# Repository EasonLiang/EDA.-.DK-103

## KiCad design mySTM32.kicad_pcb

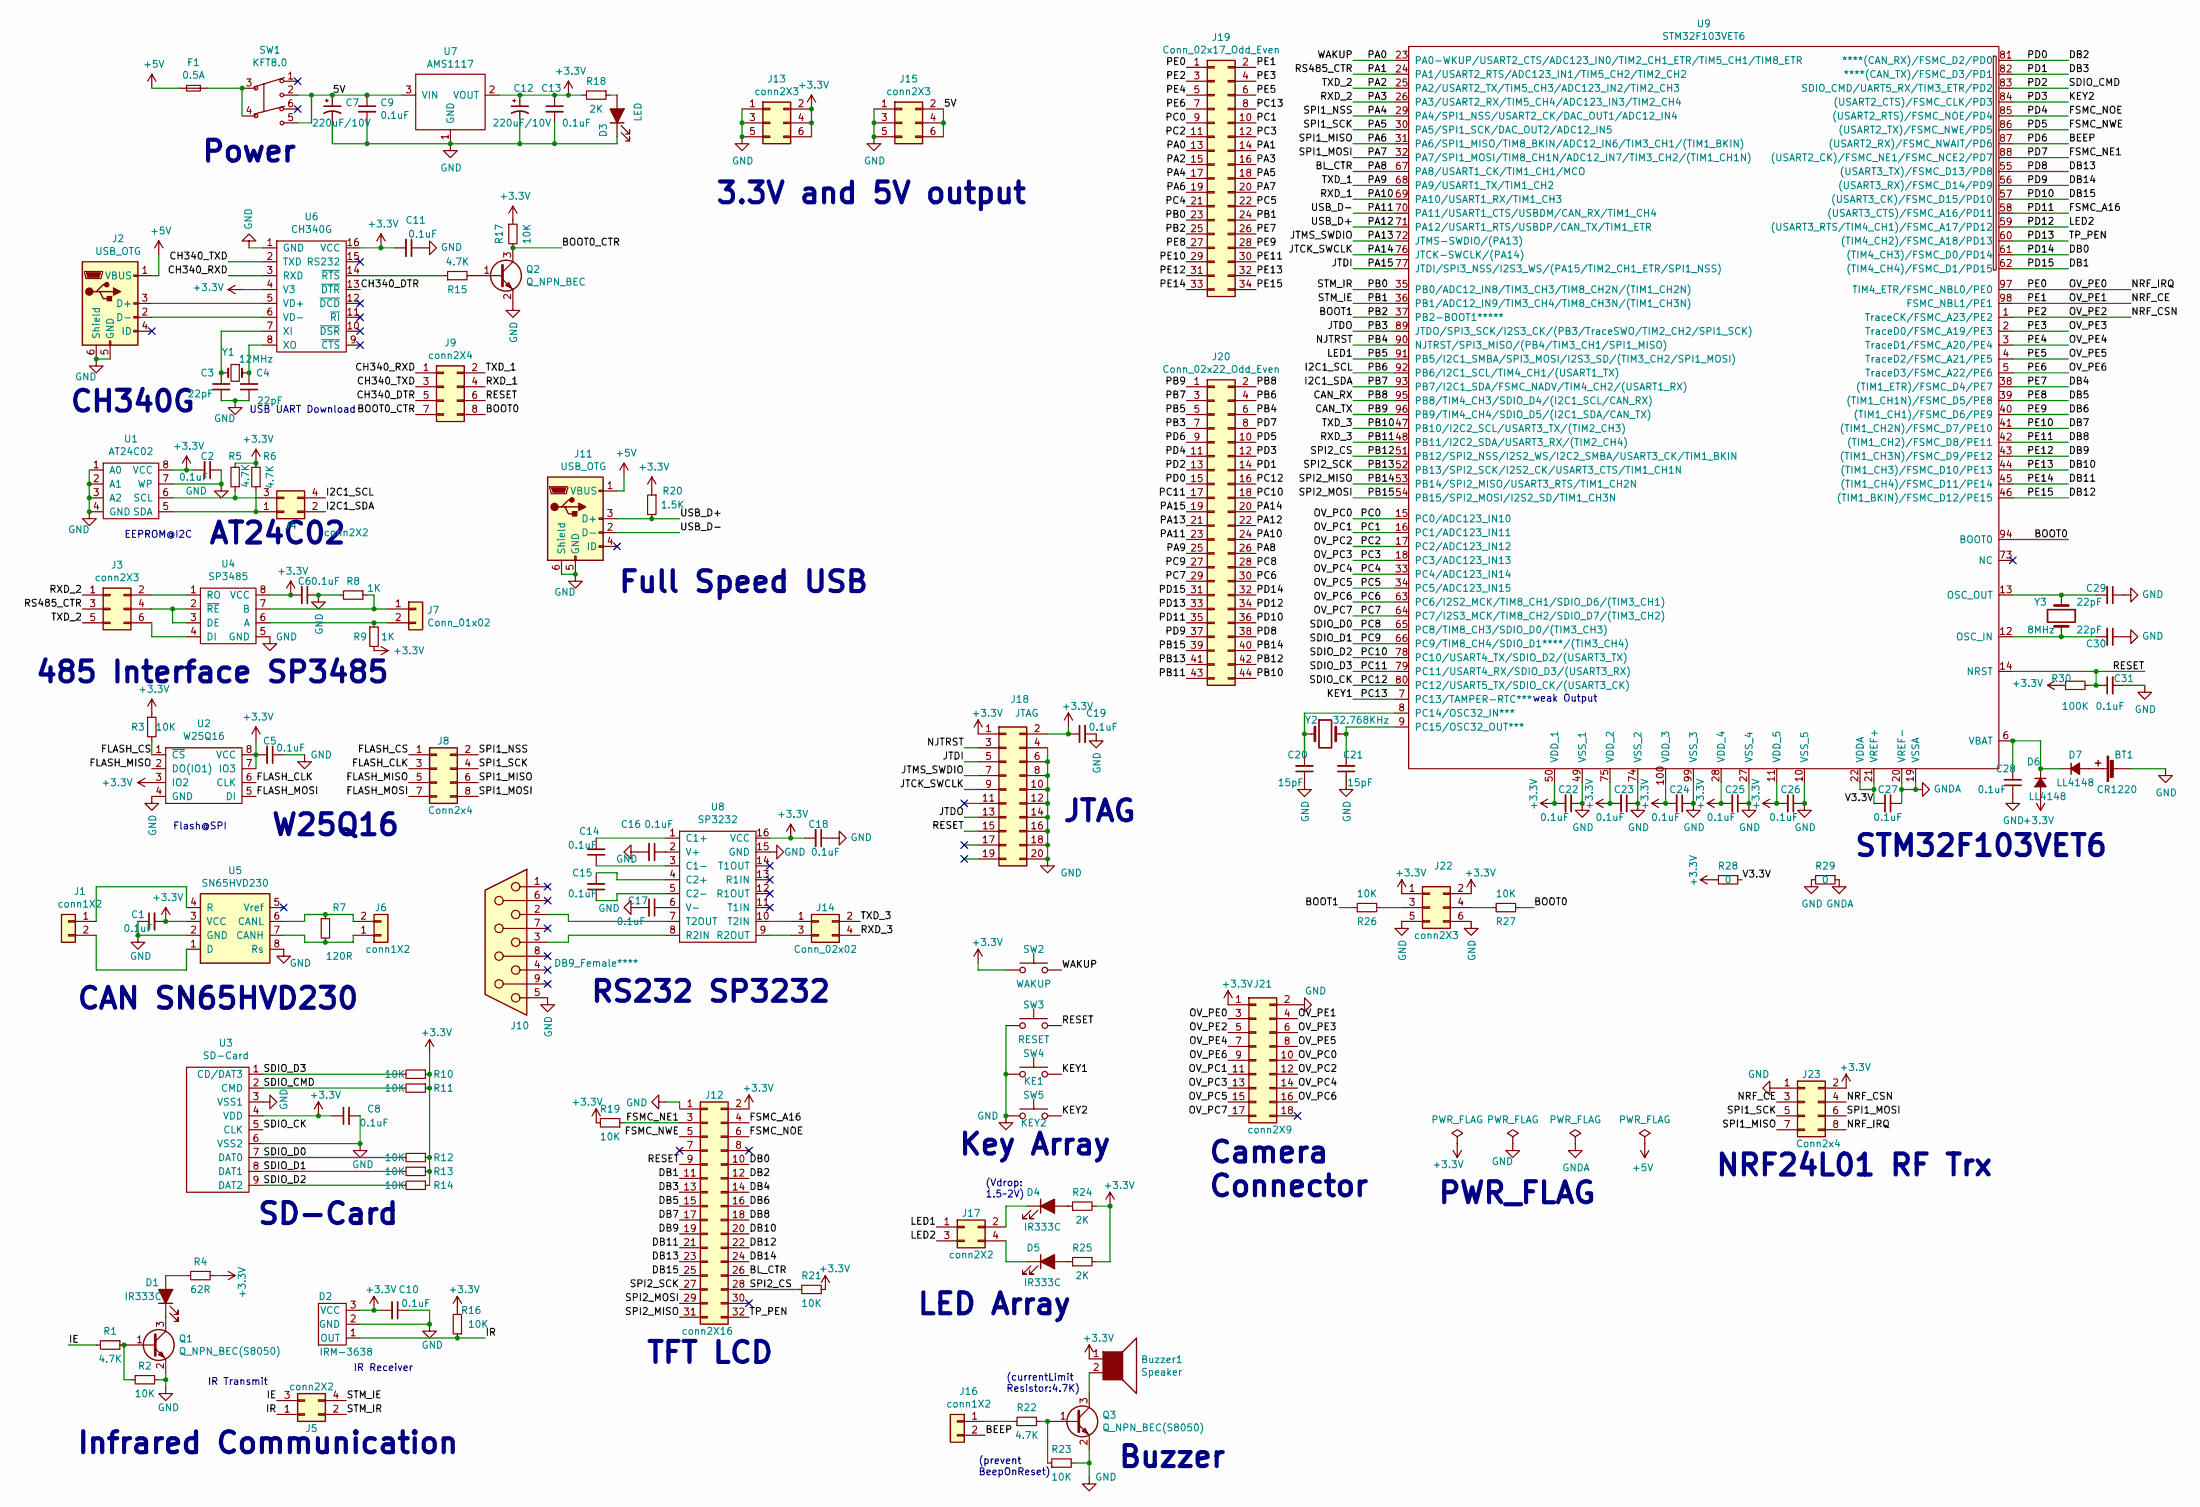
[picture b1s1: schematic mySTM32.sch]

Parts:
BT1: CR1220
Buzzer1: Speaker; BEEP9X5.5
C1, C2, C5, C6, C8, C10, C11, C14, C15, C16, C17, C18, C19, C22, C23, C24, C25, C26, C27, C28, C31: 0.1uF; C_0603_1608Metric
C3, C4, C29, C30: 22pF; C_0603_1608Metric
C7, C12: 220uF/10V; CP_Elec_6.3x5.7
C9, C13: 0.1uF; C_0805_2012Metric
C20, C21: 15pF; C_0603_1608Metric
D1: IR333C
D2: IRM-3638
D3: LED; LED_0805
D4, D5: IR333C; LED_0805
D6, D7: LL4148; LL34
F1: 0.5A; R_0805_2012Metric
J1, J16: conn1X2; CON1X2
J2, J11: USB_OTG; USB_Mini-B_Lumberg_2486_01_Horizontal
J3, J13, J15, J22: conn2X3; CON2X3
J4, J5, J17: conn2X2; CON2X2
J6: conn1X2; WJ301V-5.00-2P
J7: Conn_01x02; WJ301V-5.00-2P
J8, J23: Conn2x4; CON2X4
J9: conn2X4; CON2X4
J10: DB9_Female****; DB9FC
J12: conn2X16; CON2X16
J14: Conn_02x02; CON2X2
J18: JTAG; IDC-Header_2x10_P2.54mm_Vertical
J19: Conn_02x17_Odd_Even; CON2X17
J20: Conn_02x22_Odd_Even; CON2X22
J21: conn2X9; CON2X9
Q1, Q3: Q_NPN_BEC(S8050); SOT-23
Q2: Q_NPN_BEC; SOT-23
R1, R5, R6, R15, R22: 4.7K; R_0603_1608Metric
R2, R3, R10, R11, R12, R13, R14, R16, R17, R19, R21, R23, R26, R27: 10K; R_0603_1608Metric
R4: 62R; R_0805_2012Metric
R7: 120R; R_0603_1608Metric
R8, R9: 1K; R_0603_1608Metric
R18, R24, R25: 2K; R_0603_1608Metric
R20: 1.5K; R_0603_1608Metric
R28, R29: 0; R_0603_1608Metric
R30: 100K; R_0603_1608Metric
SW1: KFT8.0
SW2: WAKUP; KEY6X6
SW3: RESET; KEY6X6
SW4: KE1; KEY6X6
SW5: KEY2; KEY6X6
U1: AT24C02; SOIC-8
U2: W25Q16; WSOP-8
U3: SD-Card
U4: SP3485; SOIC-8
U5: SN65HVD230; SOIC-8
U6: CH340G; SOIC-16
U7: AMS1117; SOT-223
U8: SP3232; SOIC-16
U9: STM32F103VET6; LQFP-100
Y1: 12MHz; Crystal_HC49-U_Vertical
Y2: 32.768KHz; Crystal_SMD_3215-2Pin_3.2x1.5mm
Y3: 8MHz; Crystal_HC49-U_Vertical

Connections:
+3V3: Buzzer1.1, C1.2, C2.2, C5.2, C6.2, C8.1, C10.2, C11.2, C12.1, C13.1, C18.2, C19.1, C22.2, C23.2, C24.2, C25.2, C26.2, D2.3 (VCC), D6.2 (A), J12.2, J13.2, J13.4, J13.6, J18.1, J18.2, J21.1, J22.1, J22.2, J23.2, R3.1, R4.1, R5.2, R6.2, R9.2, R10.1, R11.1, R12.1, R13.1, R14.1, R16.2, R17.1, R18.2, R19.2, R20.1, R21.2, R24.2, R25.2, R28.2, R30.1, SW2.1, U1.8 (VCC), U2.3 (IO2), U2.7 (IO3), U2.8 (VCC), U3.4 (VDD), U4.8 (VCC), U5.3 (VCC), U6.4 (V3), U6.16 (VCC), U7.2 (VOUT), U8.16 (VCC), U9.11 (VDD_5), U9.28 (VDD_4), U9.50 (VDD_1), U9.75 (VDD_2), U9.100 (VDD_3)
+5V: F1.1, J2.1 (VBUS), J11.1 (VBUS)
/5V: C7.1, C9.1, J15.2, J15.4, J15.6, SW1.2, SW1.5, U7.3 (VIN)
/BEEP: J16.2, J20.9, U9.87 ((USART2_RX)/FSMC_NWAIT/PD6)
/BL_CTR: J12.26, J20.26, U9.67 (PA8/USART1_CK/TIM1_CH1/MCO)
/BOOT0: J9.8, R27.2, U9.94 (BOOT0)
/BOOT0_CTR: J9.7, Q2.3 (C), R17.2
/BOOT1: J19.25, R26.1, U9.37 (PB2-BOOT1*****)
/CAN_RX: J20.2, U9.95 (PB8/TIM4_CH3/SDIO_D4/(I2C1_SCL/CAN_RX))
/CAN_TX: J20.1, U9.96 (PB9/TIM4_CH4/SDIO_D5/(I2C1_SDA/CAN_TX))
/CH340_DTR: J9.5, U6.13 (~DTR~)
/CH340_RXD: J9.1, U6.3 (RXD)
/CH340_TXD: J9.3, U6.2 (TXD)
/DB0: J12.10, J20.32, U9.61 ((TIM4_CH3)/FSMC_D0/PD14)
/DB1: J12.11, J20.31, U9.62 ((TIM4_CH4)/FSMC_D1/PD15)
/DB2: J12.12, J20.15, U9.81 (****(CAN_RX)/FSMC_D2/PD0)
/DB3: J12.13, J20.14, U9.82 (****(CAN_TX)/FSMC_D3/PD1)
/DB4: J12.14, J19.26, U9.38 ((TIM1_ETR)/FSMC_D4/PE7)
/DB5: J12.15, J19.27, U9.39 ((TIM1_CH1N)/FSMC_D5/PE8)
/DB6: J12.16, J19.28, U9.40 ((TIM1_CH1)/FSMC_D6/PE9)
/DB7: J12.17, J19.29, U9.41 ((TIM1_CH2N)/FSMC_D7/PE10)
/DB8: J12.18, J19.30, U9.42 ((TIM1_CH2)/FSMC_D8/PE11)
/DB9: J12.19, J19.31, U9.43 ((TIM1_CH3N)/FSMC_D9/PE12)
/DB10: J12.20, J19.32, U9.44 ((TIM1_CH3)/FSMC_D10/PE13)
/DB11: J12.21, J19.33, U9.45 ((TIM1_CH4)/FSMC_D11/PE14)
/DB12: J12.22, J19.34, U9.46 ((TIM1_BKIN)/FSMC_D12/PE15)
/DB13: J12.23, J20.38, U9.55 ((USART3_TX)/FSMC_D13/PD8)
/DB14: J12.24, J20.37, U9.56 ((USART3_RX)/FSMC_D14/PD9)
/DB15: J12.25, J20.36, U9.57 ((USART3_CK)/FSMC_D15/PD10)
/FLASH_CLK: J8.3, U2.6 (CLK)
/FLASH_CS: J8.1, R3.2, U2.1 (~CS~)
/FLASH_MISO: J8.5, U2.2 (DO(IO1))
/FLASH_MOSI: J8.7, U2.5 (DI)
/FSMC_A16: J12.4, J20.35, U9.58 ((USART3_CTS)/FSMC_A16/PD11)
/FSMC_NE1: J12.3, J20.8, R19.1, U9.88 ((USART2_CK)/FSMC_NE1/FSMC_NCE2/PD7)
/FSMC_NOE: J12.6, J20.11, U9.85 ((USART2_RTS)/FSMC_NOE/PD4)
/FSMC_NWE: J12.5, J20.10, U9.86 ((USART2_TX)/FSMC_NWE/PD5)
/I2C1_SCL: J4.4, J20.4, U9.92 (PB6/I2C1_SCL/TIM4_CH1/(USART1_TX))
/I2C1_SDA: J4.2, J20.3, U9.93 (PB7/I2C1_SDA/FSMC_NADV/TIM4_CH2/(USART1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)
/IE: J5.3, R1.2
/IR: D2.1 (OUT), J5.1, R16.1
/JTCK_SWCLK: J18.9, J20.20, U9.76 (JTCK-SWCLK/(PA14))
/JTDI: J18.5, J20.19, U9.77 (JTDI/SPI3_NSS/I2S3_WS/(PA15/TIM2_CH1_ET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)
/JTDO: J18.13, J20.7, U9.89 (JTDO/SPI3_SCK/I2S3_CK/(PB3/TraceSWO/TIM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)
/JTMS_SWDIO: J18.7, J20.21, U9.72 (JTMS-SWDIO/(PA13))
/KEY1: J19.8, SW4.2, U9.7 (PC13/TAMPER-RTC***)
/KEY2: J20.12, SW5.2, U9.84 ((USART2_CTS)/FSMC_CLK/PD3)
/LED1: J17.1, J20.5, U9.91 (PB5/I2C1_SMBA/SPI3_MOSI/I2S3_SD/(TIM3_C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)
/LED2: J17.3, J20.34, U9.59 ((USART3_RTS/TIM4_CH1)/FSMC_A17/PD12)
/NJTRST: J18.3, J20.6, U9.90 (NJTRST/SPI3_MISO/(PB4/TIM3_CH1/SPI1_MIS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)
/NRF_CE: J19.2, J21.4, J23.3, U9.98 (FSMC_NBL1/PE1)
/NRF_CSN: J19.3, J21.5, J23.4, U9.1 (TraceCK/FSMC_A23/PE2)
/NRF_IRQ: J19.1, J21.3, J23.8, U9.97 (TIM4_ETR/FSMC_NBL0/PE0)
/OV_PC0: J19.9, J21.10, U9.15 (PC0/ADC123_IN10)
/OV_PC1: J19.10, J21.11, U9.16 (PC1/ADC123_IN11)
/OV_PC2: J19.11, J21.12, U9.17 (PC2/ADC123_IN12)
/OV_PC3: J19.12, J21.13, U9.18 (PC3/ADC123_IN13)
/OV_PC4: J19.21, J21.14, U9.33 (PC4/ADC123_IN14)
/OV_PC5: J19.22, J21.15, U9.34 (PC5/ADC123_IN15)
/OV_PC6: J20.30, J21.16, U9.63 (PC6/I2S2_MCK/TIM8_CH1/SDIO_D6/(TIM3_CH1))
/OV_PC7: J20.29, J21.17, U9.64 (PC7/I2S3_MCK/TIM8_CH2/SDIO_D7/(TIM3_CH2))
/OV_PE3: J19.4, J21.6, U9.2 (TraceD0/FSMC_A19/PE3)
/OV_PE4: J19.5, J21.7, U9.3 (TraceD1/FSMC_A20/PE4)
/OV_PE5: J19.6, J21.8, U9.4 (TraceD2/FSMC_A21/PE5)
/OV_PE6: J19.7, J21.9, U9.5 (TraceD3/FSMC_A22/PE6)
/PA0: J19.13, SW2.2, U9.23 (PA0-WKUP/USART2_CTS/ADC123_IN0/TIM2_CH1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)
/PA1: J3.3, J19.14, U9.24 (PA1/USART2_RTS/ADC123_IN1/TIM5_CH2/TIM2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)
/PA2: J3.5, J19.15, U9.25 (PA2/USART2_TX/TIM5_CH3/ADC123_IN2/TIM2_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)
/PA3: J3.1, J19.16, U9.26 (PA3/USART2_RX/TIM5_CH4/ADC123_IN3/TIM2_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)
/PA4: J8.2, J19.17, U9.29 (PA4/SPI1_NSS/USART2_CK/DAC_OUT1/ADC12_I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)
/PA5: J8.4, J19.18, J23.5, U9.30 (PA5/SPI1_SCK/DAC_OUT2/ADC12_IN5)
/PA6: J8.6, J19.19, J23.7, U9.31 (PA6/SPI1_MISO/TIM8_BKIN/ADC12_IN6/TIM3_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)
/PA7: J8.8, J19.20, J23.6, U9.32 (PA7/SPI1_MOSI/TIM8_CH1N/ADC12_IN7/TIM3_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)
/PA9: J9.2, J20.25, U9.68 (PA9/USART1_TX/TIM1_CH2)
/PA10: J9.4, J20.24, U9.69 (PA10/USART1_RX/TIM1_CH3)
/PA11: J11.2 (D-), J20.23, U9.70 (PA11/USART1_CTS/USBDM/CAN_RX/TIM1_CH4)
/PA12: J11.3 (D+), J20.22, R20.2, U9.71 (PA12/USART1_RTS/USBDP/CAN_TX/TIM1_ETR)
/PB0: J5.2, J19.23, U9.35 (PB0/ADC12_IN8/TIM3_CH3/TIM8_CH2N/(TIM1_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)
/PB1: J5.4, J19.24, U9.36 (PB1/ADC12_IN9/TIM3_CH4/TIM8_CH3N/(TIM1_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)
/PB10: J14.2, J20.44, U9.47 (PB10/I2C2_SCL/USART3_TX/(TIM2_CH3))
/PB11: J14.4, J20.43, U9.48 (PB11/I2C2_SDA/USART3_RX/(TIM2_CH4))
/PB12: J12.28, J20.42, R21.1, U9.51 (PB12/SPI2_NSS/I2S2_WS/I2C2_SMBA/USART3_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)
/PB13: J12.27, J20.41, U9.52 (PB13/SPI2_SCK/I2S2_CK/USART3_CTS/TIM1_C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)
/PB14: J12.31, J20.40, U9.53 (PB14/SPI2_MISO/USART3_RTS/TIM1_CH2N)
/PB15: J12.29, J20.39, U9.54 (PB15/SPI2_MOSI/I2S2_SD/TIM1_CH3N)
/PC8: J20.28, R12.2, U3.7 (DAT0), U9.65 (PC8/TIM8_CH3/SDIO_D0/(TIM3_CH3))
/PC9: J20.27, R13.2, U3.8 (DAT1), U9.66 (PC9/TIM8_CH4/SDIO_D1****/(TIM3_CH4))
/PC10: J20.18, R14.2, U3.9 (DAT2), U9.78 (PC10/USART4_TX/SDIO_D2/(USART3_TX))
/PC11: J20.17, R10.2, U3.1 (CD/DAT3), U9.79 (PC11/USART4_RX/SDIO_D3/(USART3_RX))
/PC12: J20.16, U3.5 (CLK), U9.80 (PC12/USART5_TX/SDIO_CK/(USART3_CK))
/PD2: J20.13, R11.2, U3.2 (CMD), U9.83 (SDIO_CMD/UART5_RX/TIM3_ETR/PD2)
/PD13: J12.32, J20.33, U9.60 ((TIM4_CH2)/FSMC_A18/PD13)
/RESET: C31.1, J9.6, J12.9, J18.15, R30.2, SW3.2, U9.14 (NRST)
/V3.3V: C27.2, R28.1, U9.21 (VREF+), U9.22 (VDDA)
GND: BT1.2 (-), C1.1, C2.1, C3.1, C4.1, C5.1, C6.1, C7.2, C8.2, C9.2, C10.1, C11.1, C12.2, C13.2, C16.2, C17.2, C18.1, C19.2, C20.1, C21.1, C22.1, C23.1, C24.1, C25.1, C26.1, C28.1, C29.1, C30.1, C31.2, D2.2 (GND), D3.1 (K), J2.5 (GND), J2.6 (Shield), J10.5, J11.5 (GND), J11.6 (Shield), J12.1, J13.1, J13.3, J13.5, J15.1, J15.3, J15.5, J18.4, J18.6, J18.8, J18.10, J18.12, J18.14, J18.16, J18.18, J18.20, J21.2, J22.5, J22.6, J23.1, Q1.2 (E), Q2.2 (E), Q3.2 (E), R2.1, R8.2, R23.2, R29.2, SW3.1, SW4.1, SW5.1, U1.1 (A0), U1.2 (A1), U1.3 (A2), U1.4 (GND), U1.7 (WP), U2.4 (GND), U3.3 (VSS1), U3.6 (VSS2), U4.5 (GND), U5.2 (GND), U5.8 (Rs), U6.1 (GND), U7.1 (GND), U8.15 (GND), U9.10 (VSS_5), U9.27 (VSS_4), U9.49 (VSS_1), U9.74 (VSS_2), U9.99 (VSS_3)
GNDA: C27.1, R29.1, U9.19 (VSSA), U9.20 (VREF-)
unnamed: BT1.1 (+), D7.2 (A)
unnamed: Buzzer1.2, Q3.3 (C)
unnamed: C3.2, U6.7 (XI), Y1.2
unnamed: C4.2, U6.8 (XO), Y1.1
unnamed: C14.1, U8.3 (C1-)
unnamed: C14.2, U8.1 (C1+)
unnamed: C15.1, U8.5 (C2-)
unnamed: C15.2, U8.4 (C2+)
unnamed: C16.1, U8.2 (V+)
unnamed: C17.1, U8.6 (V-)
unnamed: C20.2, U9.8 (PC14/OSC32_IN***), Y2.1
unnamed: C21.2, U9.9 (PC15/OSC32_OUT***), Y2.2
unnamed: C28.2, D6.1 (K), D7.1 (K), U9.6 (VBAT)
unnamed: C29.2, U9.13 (OSC_OUT), Y3.1
unnamed: C30.2, U9.12 (OSC_IN), Y3.2
unnamed: D1.1 (K), Q1.3 (C)
unnamed: D1.2 (A), R4.2
unnamed: D3.2 (A), R18.1
unnamed: D4.1 (K), J17.2
unnamed: D4.2 (A), R24.1
unnamed: D5.1 (K), J17.4
unnamed: D5.2 (A), R25.1
unnamed: F1.2, SW1.3, SW1.4
unnamed: J1.1, U5.4 (R)
unnamed: J1.2, U5.1 (D)
unnamed: J2.2 (D-), U6.6 (VD-)
unnamed: J2.3 (D+), U6.5 (VD+)
unnamed: J3.2, U4.1 (RO)
unnamed: J3.4, U4.2 (~RE~), U4.3 (DE)
unnamed: J3.6, U4.4 (DI)
unnamed: J4.1, R6.1, U1.5 (SDA)
unnamed: J4.3, R5.1, U1.6 (SCL)
unnamed: J6.1, R7.2, U5.7 (CANH)
unnamed: J6.2, R7.1, U5.6 (CANL)
unnamed: J7.1, R8.1, U4.7 (B)
unnamed: J7.2, R9.1, U4.6 (A)
unnamed: J10.2, U8.7 (T2OUT)
unnamed: J10.3, U8.8 (R2IN)
unnamed: J14.1, U8.10 (T2IN)
unnamed: J14.3, U8.9 (R2OUT)
unnamed: J16.1, R22.1
unnamed: J22.3, R26.2
unnamed: J22.4, R27.1
unnamed: Q1.1 (B), R1.1, R2.2
unnamed: Q2.1 (B), R15.2
unnamed: Q3.1 (B), R22.2, R23.1
unnamed: R15.1, U6.14 (~RTS~)

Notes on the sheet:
EEPROM@I2C
485 Interface SP3485
Flash@SPI
CAN SN65HVD230
USB UART Download
Full Speed USB
IR Transmit
SD-Card
JTAG
IR Receiver
TFT LCD
weak Output
Key Array
(Vdrop: 1.5~~2V)
LED Array
(currentLimit Resistor:4.7K)
(prevent BeepOnReset)
Camera Connector
NRF24L01 RF Trx
RS232 SP3232
Power
3.3V and 5V output
CH340G
W25Q16
AT24C02
Infrared Communication
Buzzer
PWR_FLAG
STM32F103VET6

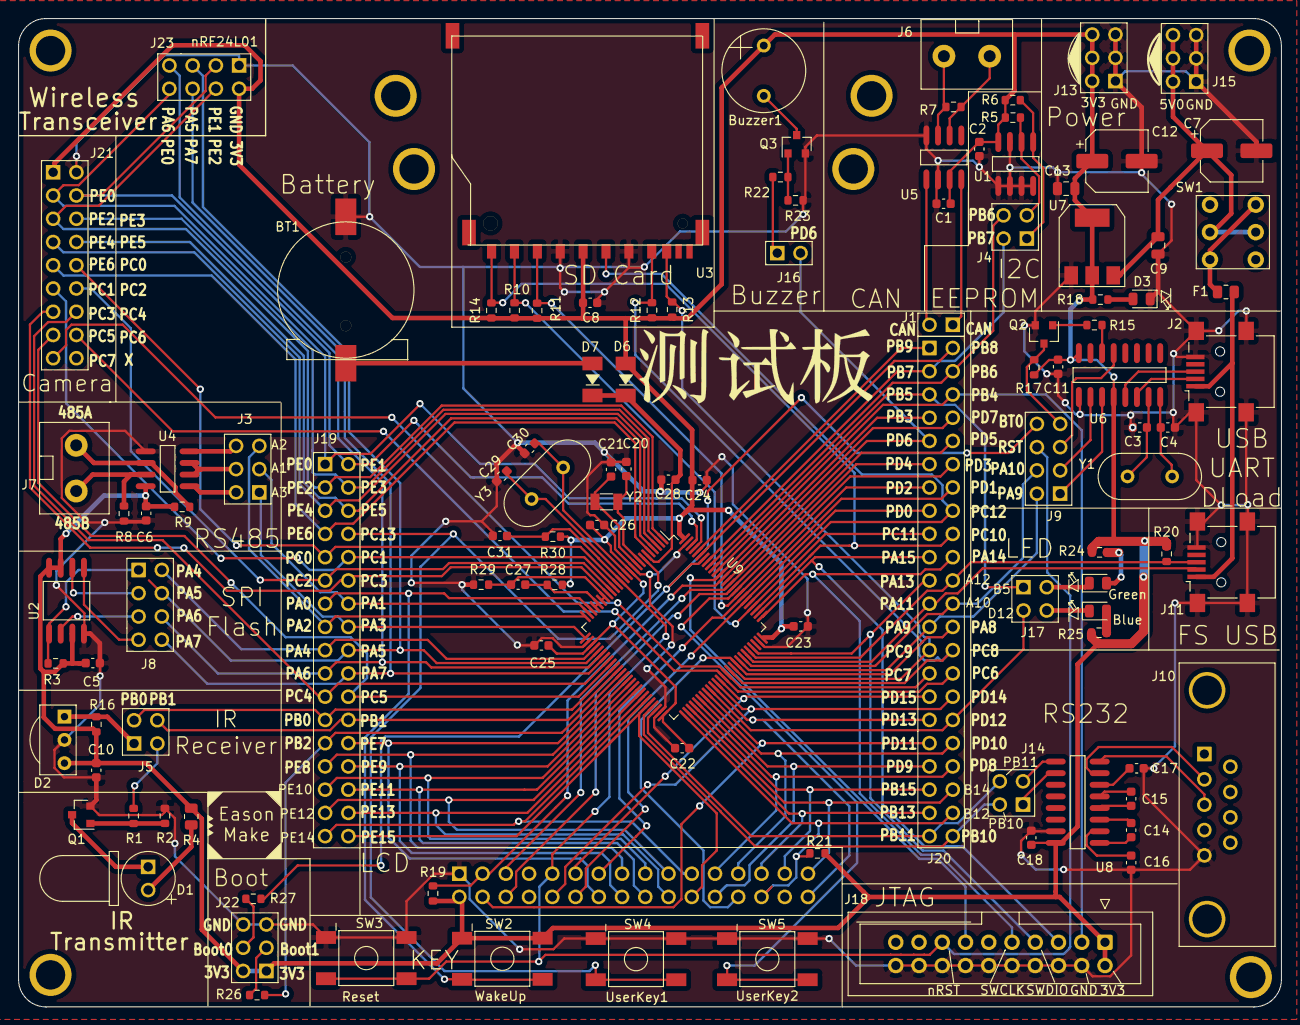
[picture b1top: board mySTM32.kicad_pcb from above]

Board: 2 copper layers, 138.0 x 108.0 mm, 113 parts (1 on the bottom side), 143 nets.

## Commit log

2021-07-22 Initialization
2021-07-24 [outline] change to 138*108mm [notes] notes on LED, Diode , IR, UserKey [align] left , right and LCD connector
2021-07-24 [assembly] LCD connector [other] re-Layout
2021-07-24 [right connector] [trace width] to 10mil
2021-07-24 [left connector] [crystal]
2021-07-24 [power]
2021-07-24 [usb2uart, uart download]
2021-07-24 [I2C EEPROM] [schematic validation on I2C ]
2021-07-24 [can]
2021-07-24 [buzzer, lib] [layout] SD-Card
2021-07-24 [FS USB] [LED] [Conn Annotation]
2021-07-24 [RS232]
2021-07-24 [IR Tx] [IR Rx]
2021-07-24 [SPI Flash]
2021-07-24 [RS485]
2021-07-24 [JTAG]
2021-07-24 [Battery] route, footprint pad [Decouple Cap]
2021-07-25 [sd-card]
2021-07-25 [Camera]
2021-07-25 [RF2.4G]
2021-07-25 [TFT-LCD]
2021-07-25 [Key Array]
2021-07-26 [boot] partial
2021-07-26 [Power] [Boot] [Reset] [nRF IRQ/CE]
2021-07-26 [Annotation]
2021-07-27 [Ground]
2021-07-27 [DRC]
2021-07-27 [LogoSilk] on Top ; [LogoNegativeMask] on Bottom
2021-07-27 [Pour Copper]
2021-07-29 [Gerber] [Drill] files
